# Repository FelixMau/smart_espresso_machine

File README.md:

# smart espresso machine

A hobby project to digitalise and IoT-enable my **Dalla Corte Mini** espresso machine (and maybe other machines in the future).

Unlike [Gaggiuino](https://gaggiuino.github.io/#/?id=home) or [GaggiMate](https://gaggimate.eu/), the goal here is **not** to replace the machine's original controls but to **extend** them. This way we don't have to mingle so much with high voltages, and the machine stays fully restorable to stock.

An ESP32 reads a Bluetooth scale and a pressure sensor, drives the pump via a PWM dimmer with a PID pressure controller, and uses linear regression to predict when a shot reaches its target weight — stopping extraction at the optimal moment. Everything is monitored and controlled live from a web dashboard on the LAN.

## How this compares to Gaggiuino & GaggiMate

Both projects turn cheap single-boiler machines (Gaggia Classic, Rancilio Silvia) into smart ones by taking over the heater, pump and steam control. This project serves a different niche:

| | Gaggiuino / GaggiMate | This project |
|---|---|---|
| Target machine | Single-boiler entry-level | Dual-boiler prosumer (Dalla Corte Mini) |
| Integration | Replaces the machine's controls | Extends them (opto-isolated button presses) — restorable to stock |
| Temperature & steam | PID heater + steam control | Not needed — the dual boiler already does this |
| Display | Installed touchscreen | Headless — a spare phone / any browser is the screen |
| Brew by weight | Yes | Yes, with regression-based predictive stop and auto-learned drip offset |
| Pressure profiling | Yes (Gaggiuino also flow) | Yes — time-based profiles with PID pump control |
| App integration | Beanconqueror (Gaggiuino) | Beanconqueror, via Gaggiuino-compatible API |

## Dashboard

Live monitoring, start/stop/reset, PID tuning, goal weight and pressure profile editing, plus live charts and a shot-history comparison — all served from the ESP32.

<!-- Add real screenshots to the assets/ folder (see assets/README.md) -->

## Features

- [x] Connect the scale to the microcontroller
- [x] Microcontroller can read the *shot button* from the machine
- [x] Microcontroller is able to also 'press' the *shot button*
- [x] Design a PCB to hold the sensors
- [x] Microcontroller adjusts pump power via a dimmer
- [x] Mechanical knob to *manually* adjust pump power during shots
- [x] Add pressure sensor
- [x] PID-controlled pressure profiles (live-tunable over the web)
- [x] Predictive shot stopping via linear regression on weight-vs-time
- [x] EEPROM auto-learning of the weight offset after each shot
- [x] Async web dashboard: live tiles, charts, control and tuning
- [ ] Pressure sensor readings shown on a simple on-device display
- [ ] Design cases for PCB, display, knob
- [ ] Design import to beanconqueror -> custom machine
should be able to start shot via app
- [x] Implement correct zero crosing detection and update pwm control accordingly
- [ ] Cleaning mode/cycle for descale and for detergent
- [ ] If no Wifi is available advertise own wifi and on it the webserver to do the same as on the local network
- [ ] Add another (manual)pressuresensor to evaluate accuracy of messurements, they sometimes feel a little off or I should adjust the expansionvalve

### Repository layout
```
firmware/    ESP32 firmware (PlatformIO)  →  platformio run -d firmware -e upesy_wroom
android/     Phone app (Gradle/Kotlin)    →  cd android && ./gradlew assembleDebug
pcb/         KiCad project and gerbers
datasheets/  Datasheets
```

### Android app
There is a phone app in [`android/`](android/README.md): live readings, start/stop,
goal weight, weight offset and the pressure profile editor, plus a journal that
stores every shot's weight/pressure curve on the phone and charts it.

It talks to the JSON API the ESP32 serves on the local network (see
[`firmware/src/webserver.cpp`](firmware/src/webserver.cpp)).

### Future tasks:

- [ ] Check on 230V safety and how to design properly with 230V on a espressomachine (that uses heats up water and puts it under pressure)
- [ ] Expose machine to internet? IDK this leads to many questions needing answeres such as how and which ports would need to be opened? Xiaomi robo cleaner does that somehow but I dont know how yet. Also password would be needed to log in -> or some local setup would provide a "password" via the app internally but all of this seems like a hustle for just the little benefit of no need to connect to local wifi....
- [ ] How could I sense the watertank fill status?

## Working details

- **Scale**: Acaia Lunar, via [@tatemazer's AcaiaArduinoBLE](https://github.com/tatemazer/AcaiaArduinoBLE) library.
- **Microcontroller**: ESP32 (upesy_wroom), firmware built with PlatformIO.
- **Button read/write**: via optocouplers, so the ESP never touches the machine's high-voltage logic.
- **Pump control**: PWM signal to the dimmer (zero-crossing functionality not yet working).
- **Manual override**: an encoder knob controls pump power (handy while work is in progress).
- **Architecture**: separate FreeRTOS tasks for BLE, the control loop, and the web server, so a missing scale or busy web client can never stall brewing. Boots and brews without WiFi and without the scale.

## Getting started

```bash
# 1. Provide WiFi credentials (this file is gitignored — never commit it)
cp firmware/src/secrets.h.example firmware/src/secrets.h   # then edit ssid / password

# 2. Build and upload
platformio run -d firmware -e upesy_wroom
platformio run -d firmware -e upesy_wroom --target upload

# 3. Watch serial output (dashboard URL is printed periodically)
platformio device monitor -d firmware
```

The dashboard is then reachable at the IP the ESP32 prints on the serial console.

## PCB

The KiCad design lives in `pcb/`. Latest revision:

- [x] Added lights / power connections
- [x] Corrected false routing
- [x] Corrected optocoupler footprints
- [x] Added on/off switch to save power on the ESP
- [x] Got a second opinion on the PCB design
- [x] Added interface for a potential display

## License

Licensed under the **GNU General Public License v3.0** — see [LICENSE](LICENSE).

Copyright © 2026 Felix Maurer.

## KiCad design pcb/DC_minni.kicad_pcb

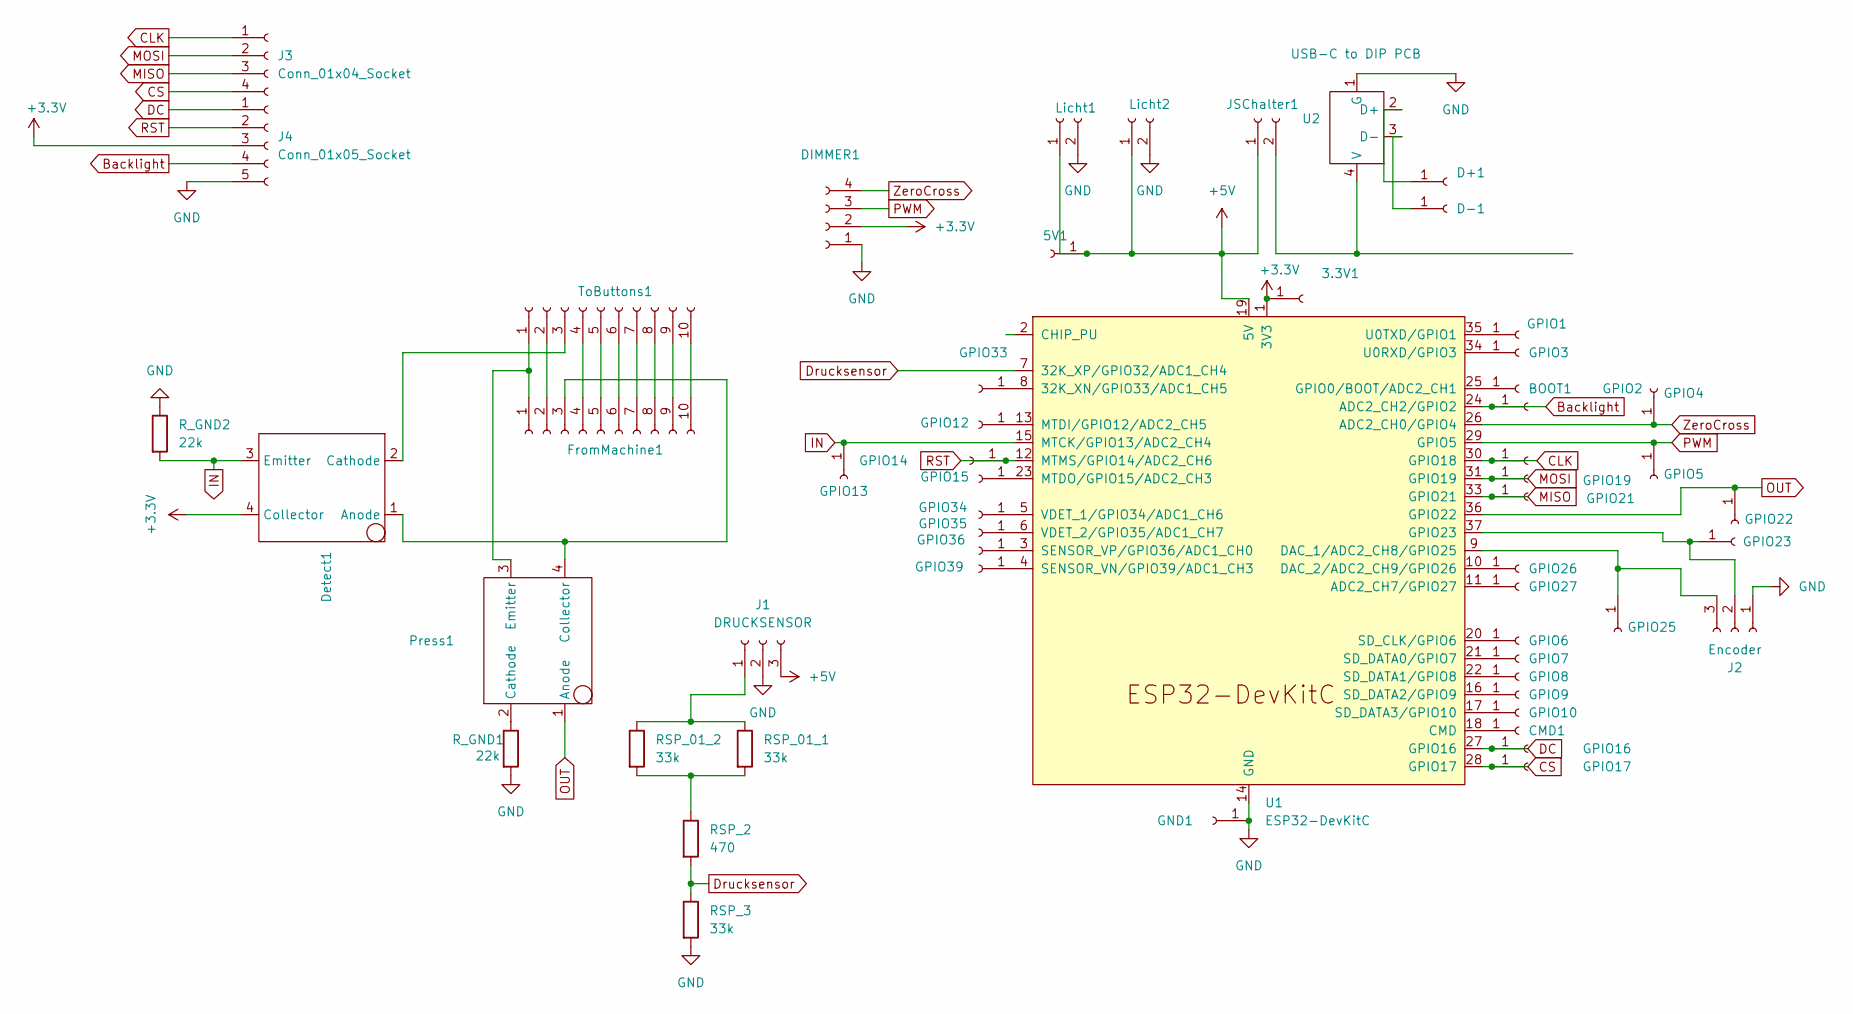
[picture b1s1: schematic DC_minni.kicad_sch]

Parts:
3.3V1, 5V1: Conn_01x01_Socket; PinHeader_1x01_P2.54mm_Vertical
BOOT1: Conn_01x01_Socket; PinHeader_1x01_P2.54mm_Vertical
CMD1: Conn_01x01_Socket; PinHeader_1x01_P2.54mm_Vertical
D+1: Conn_01x01_Socket; PinHeader_1x01_P2.54mm_Vertical
D-1: Conn_01x01_Socket; PinHeader_1x01_P2.54mm_Vertical
DIMMER1: Conn_01x04_Socket; JST_XH_B4B-XH-A_1x04_P2.50mm_Vertical
Detect1: HCPL-817
FromMachine1: Conn_01x10_Socket; IDC-Header_2x05_P2.54mm_Vertical
GND1: Conn_01x01_Socket; PinHeader_1x01_P2.54mm_Vertical
GPIO1, GPIO2, GPIO3, GPIO4, GPIO5, GPIO6, GPIO7, GPIO8, GPIO9, GPIO10, GPIO12, GPIO13, GPIO14, GPIO15, GPIO16, GPIO17, GPIO18, GPIO19, GPIO21, GPIO22, GPIO23, GPIO25, GPIO26, GPIO27, GPIO33, GPIO34, GPIO35, GPIO36, GPIO39: Conn_01x01_Socket; PinHeader_1x01_P2.54mm_Vertical
J1: DRUCKSENSOR; JST_XH_B3B-XH-A_1x03_P2.50mm_Vertical
J2: Encoder; JST_XH_B3B-XH-A_1x03_P2.50mm_Vertical
J3: Conn_01x04_Socket; JST_XH_B4B-XH-A_1x04_P2.50mm_Vertical
J4: Conn_01x05_Socket; JST_XH_B5B-XH-A_1x05_P2.50mm_Vertical
JSChalter1: Conn_01x02_Socket; JST_EH_B2B-EH-A_1x02_P2.50mm_Vertical
Licht1, Licht2: Conn_01x02_Socket; JST_EH_B2B-EH-A_1x02_P2.50mm_Vertical
Press1: HCPL-817
RSP_01_1, RSP_01_2, RSP_3: 33k; R_Axial_DIN0207_L6.3mm_D2.5mm_P10.16mm_Horizontal
RSP_2: 470; R_Axial_DIN0207_L6.3mm_D2.5mm_P10.16mm_Horizontal
R_GND1, R_GND2: 22k; R_Axial_DIN0207_L6.3mm_D2.5mm_P10.16mm_Horizontal
ToButtons1: Conn_01x10_Socket; IDC-Header_2x05_P2.54mm_Vertical
U1: ESP32-DevKitC
U2: USB-C to DIP PCB; USB-C zu DIP PCB

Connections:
+3.3V: 3.3V1.1, DIMMER1.2, Detect1.4 (Collector), J4.3, U1.1 (3V3); also elsewhere on the board
+5V: 5V1.1, J1.3, JSChalter1.1, Licht1.1, Licht2.1, U1.19 (5V)
Backlight: GPIO2.1, J4.4, U1.24 (ADC2_CH2/GPIO2)
CLK: GPIO18.1, J3.1, U1.30 (GPIO18)
CS: GPIO17.1, J3.4, U1.28 (GPIO17)
DC: GPIO16.1, J4.1, U1.27 (GPIO16)
Drucksensor: RSP_2.2, RSP_3.1, U1.7 (32K_XP/GPIO32/ADC1_CH4)
GND: DIMMER1.1, GND1.1, J1.2, J2.1, J4.5, Licht1.2, Licht2.2, RSP_3.2, R_GND1.2, R_GND2.1, U1.14 (GND), U1.32 (GND), U1.38 (GND), U2.1 (G); also elsewhere on the board
IN: Detect1.3 (Emitter), GPIO13.1, R_GND2.2, U1.15 (MTCK/GPIO13/ADC2_CH4); also elsewhere on the board
MISO: GPIO21.1, J3.3, U1.33 (GPIO21)
MOSI: GPIO19.1, J3.2, U1.31 (GPIO19)
unnamed: BOOT1.1, U1.25 (GPIO0/BOOT/ADC2_CH1)
unnamed: CMD1.1, U1.18 (CMD)
unnamed: D+1.1, U2.2 (D+)
unnamed: D-1.1, U2.3 (D-)
unnamed 15: Detect1.1 (Anode), FromMachine1.3, Press1.4 (Collector); also elsewhere on the board
unnamed 16: Detect1.2 (Cathode), ToButtons1.3; also elsewhere on the board
unnamed: FromMachine1.1, Press1.3 (Emitter), ToButtons1.1
unnamed: FromMachine1.2, ToButtons1.2
unnamed: FromMachine1.4, ToButtons1.4
unnamed: FromMachine1.5, ToButtons1.5
unnamed: FromMachine1.6, ToButtons1.6
unnamed: FromMachine1.7, ToButtons1.7
unnamed: FromMachine1.8, ToButtons1.8
unnamed: FromMachine1.9, ToButtons1.9
unnamed: FromMachine1.10, ToButtons1.10
unnamed: GPIO1.1, U1.35 (U0TXD/GPIO1)
unnamed: GPIO3.1, U1.34 (U0RXD/GPIO3)
unnamed: GPIO6.1, U1.20 (SD_CLK/GPIO6)
unnamed: GPIO7.1, U1.21 (SD_DATA0/GPIO7)
unnamed: GPIO8.1, U1.22 (SD_DATA1/GPIO8)
unnamed: GPIO9.1, U1.16 (SD_DATA2/GPIO9)
unnamed: GPIO10.1, U1.17 (SD_DATA3/GPIO10)
unnamed: GPIO12.1, U1.13 (MTDI/GPIO12/ADC2_CH5)
unnamed: GPIO15.1, U1.23 (MTDO/GPIO15/ADC2_CH3)
unnamed: GPIO23.1, J2.2, U1.37 (GPIO23)
unnamed: GPIO25.1, J2.3, U1.9 (DAC_1/ADC2_CH8/GPIO25)
unnamed: GPIO26.1, U1.10 (DAC_2/ADC2_CH9/GPIO26)
unnamed: GPIO27.1, U1.11 (ADC2_CH7/GPIO27)
unnamed: GPIO33.1, U1.8 (32K_XN/GPIO33/ADC1_CH5)
unnamed: GPIO34.1, U1.5 (VDET_1/GPIO34/ADC1_CH6)
unnamed: GPIO35.1, U1.6 (VDET_2/GPIO35/ADC1_CH7)
unnamed: GPIO36.1, U1.3 (SENSOR_VP/GPIO36/ADC1_CH0)
unnamed: GPIO39.1, U1.4 (SENSOR_VN/GPIO39/ADC1_CH3)
unnamed: J1.1, RSP_01_1.1, RSP_01_2.1
unnamed: JSChalter1.2, U2.4 (V)
unnamed: Press1.2 (Cathode), R_GND1.1
unnamed: RSP_01_1.2, RSP_01_2.2, RSP_2.1
OUT: GPIO22.1, Press1.1 (Anode), U1.36 (GPIO22); also elsewhere on the board
PWM: DIMMER1.3, GPIO5.1, U1.29 (GPIO5); also elsewhere on the board
RST: GPIO14.1, J4.2, U1.12 (MTMS/GPIO14/ADC2_CH6)
ZeroCross: DIMMER1.4, GPIO4.1, U1.26 (ADC2_CH0/GPIO4); also elsewhere on the board

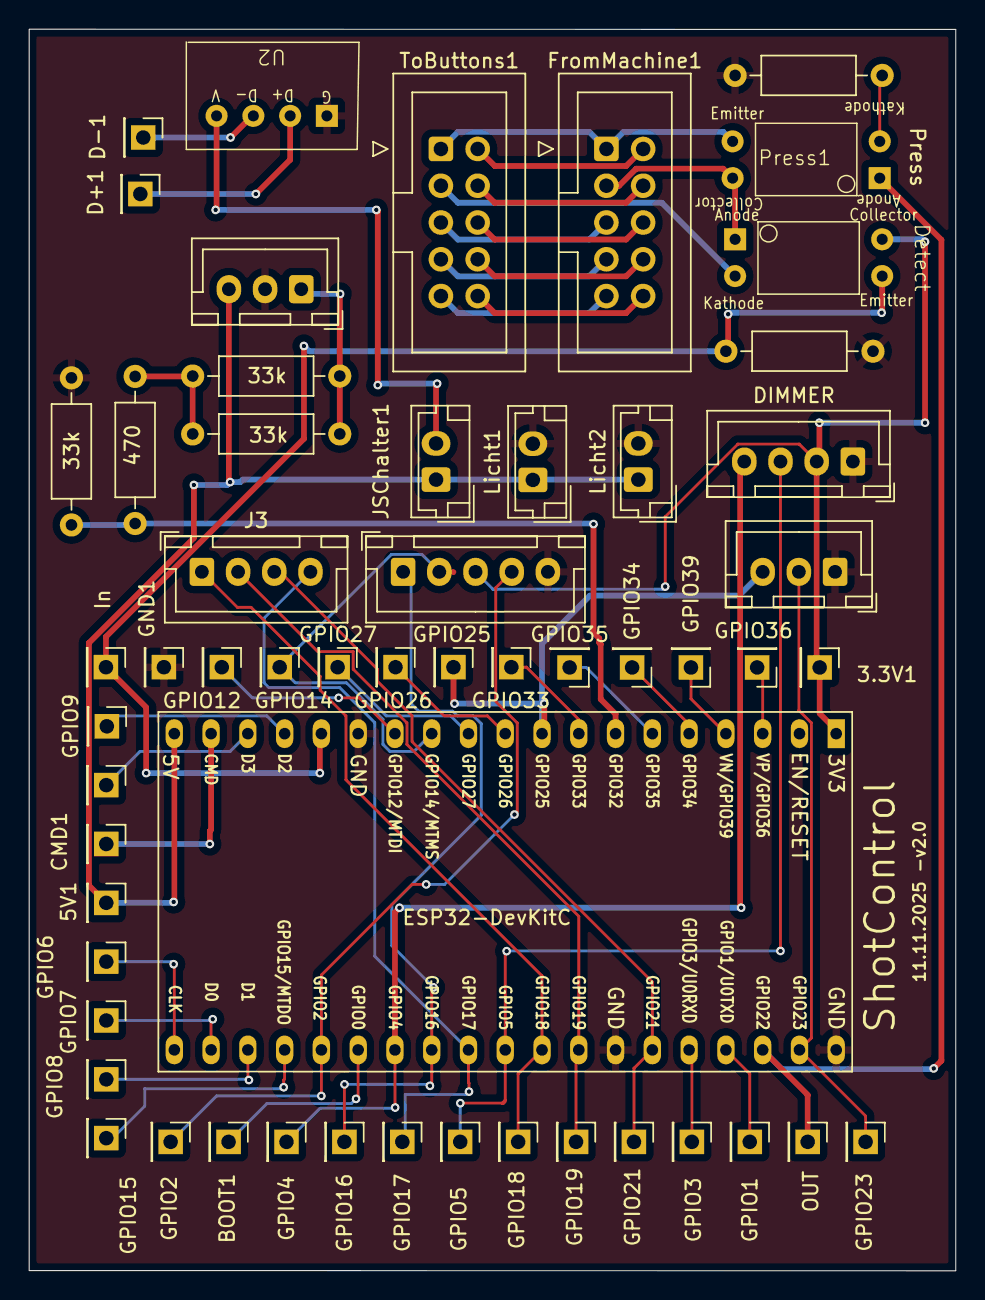
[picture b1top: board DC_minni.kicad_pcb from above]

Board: 4 copper layers, 64.0 x 85.8 mm, 56 parts (0 on the bottom side), 52 nets.

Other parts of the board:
DIMMER: Conn_01x04_Socket; JST_XH_B4B-XH-A_1x04_P2.50mm_Vertical
Detect: HCPL-817
In: Conn_01x01_Socket; PinHeader_1x01_P2.54mm_Vertical
OUT: Conn_01x01_Socket; PinHeader_1x01_P2.54mm_Vertical

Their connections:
+3.3V: DIMMER.2, Detect.4 (Collector); also elsewhere on the board
GND: DIMMER.1; also elsewhere on the board
IN: Detect.3 (Emitter), In.1; also elsewhere on the board
unnamed 15: Detect.1 (Anode); also elsewhere on the board
unnamed 16: Detect.2 (Cathode); also elsewhere on the board
OUT: OUT.1; also elsewhere on the board
PWM: DIMMER.3; also elsewhere on the board
ZeroCross: DIMMER.4; also elsewhere on the board

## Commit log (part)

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2025-05-09 starting to use input variables
2025-05-09 Working v0.0.1
2025-05-10 Working really well already. Starting shot and showing weight in server
2025-07-17 commiting
2025-07-17 Remove unused library dependency and adjust delay timing in brewing control
2025-07-18 simplifying variables to shot struct
2025-07-18 switch back buttons
2025-07-18 Adding additional debug serial prints.
2025-07-20 Remove webserver.h
2025-07-20 remove rbdimmer
2025-07-20 change pins back to as soldered
2025-07-20 fix bugs
2025-07-22 Change name of server
2025-07-22 Change to local server
2025-07-22 Restart from scratch with webserver
2025-07-22 Change goal weight in setup to read golaweight
2025-07-22 new webserver
2025-07-22 Actually pritning shot info
2025-07-22 Extend Server information
2025-07-29 Add endpoint to set goal weight via web server
2025-07-29 Revert "Add goal weight update endpoint"
2025-07-29 Add goal weight update via web
2025-07-29 Add pressure profile update
2025-07-29 Load and persist weight offset
2025-07-29 Handle negative times in pressure profile
2025-10-26 test out dimmers again
2025-10-26 renamed: src/on_hold.h -> test/on_hold.h renamed: src/secrets.h -> test/secrets.h renamed: src/shot_stopper.h -> test/shot_stopper.h renamed: src/webserver.h -> test/webserver.h
2025-10-26 Changes to be committed: modified: platformio.ini modified: src/main.cpp new file: test/SuperMon.h new file: test/shot_stopper_example.cpp new file: test/webserver_example.cpp
2025-10-26 Change
2025-10-26 Add serial print
2025-10-26 Encoder
2025-10-26 With Serials
2025-10-26 NEw encoder lib
2025-10-26 New Library
2025-10-26 New lib 2.0
2025-11-09 Adding pcb
2025-11-09 Initialize README with project details
    Added project overview and planned features for smart espresso machine.
2025-11-09 Fix spelling and formatting issues in README
    Corrected spelling errors and formatting in the README.
2025-11-11 Shematic layout adjustments
2025-11-11 Endocer Pins switch to 23 and 25
2025-11-11 Add Encoder to Schematics
2025-11-11 Add Encoder to PCB, Update layout
2025-11-11 Update PCB layout
2025-11-11 PCB routing
2025-11-11 Finished PCB routing
2025-11-11 Update README with feature completion status
2025-11-11 Implement comments from Review
2025-11-12 Combining main and old main with claude
2025-11-12 Claude Checked its own code
2025-11-12 Check if Display can be added
2025-11-12 Update README with project status
    Added a note about the project being on hold due to PCB printing costs.
2025-11-12 Update README with completed tasks and new interface
2025-11-12 Change headings from H3 to H2 in README.md
    Updated headings in README.md for better clarity and structure.
2025-11-12 Adding Display Pins to main, adjust logic for auto dimmer & Encoder interaction
2025-11-17 Updated Pcb again
2026-04-05 update pressure pin
2026-04-06 Add waiting
2026-05-14 PID controller
2026-06-13 Update Readme todos
